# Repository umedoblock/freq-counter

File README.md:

# freq-counter
frequency counter with Attiny4313

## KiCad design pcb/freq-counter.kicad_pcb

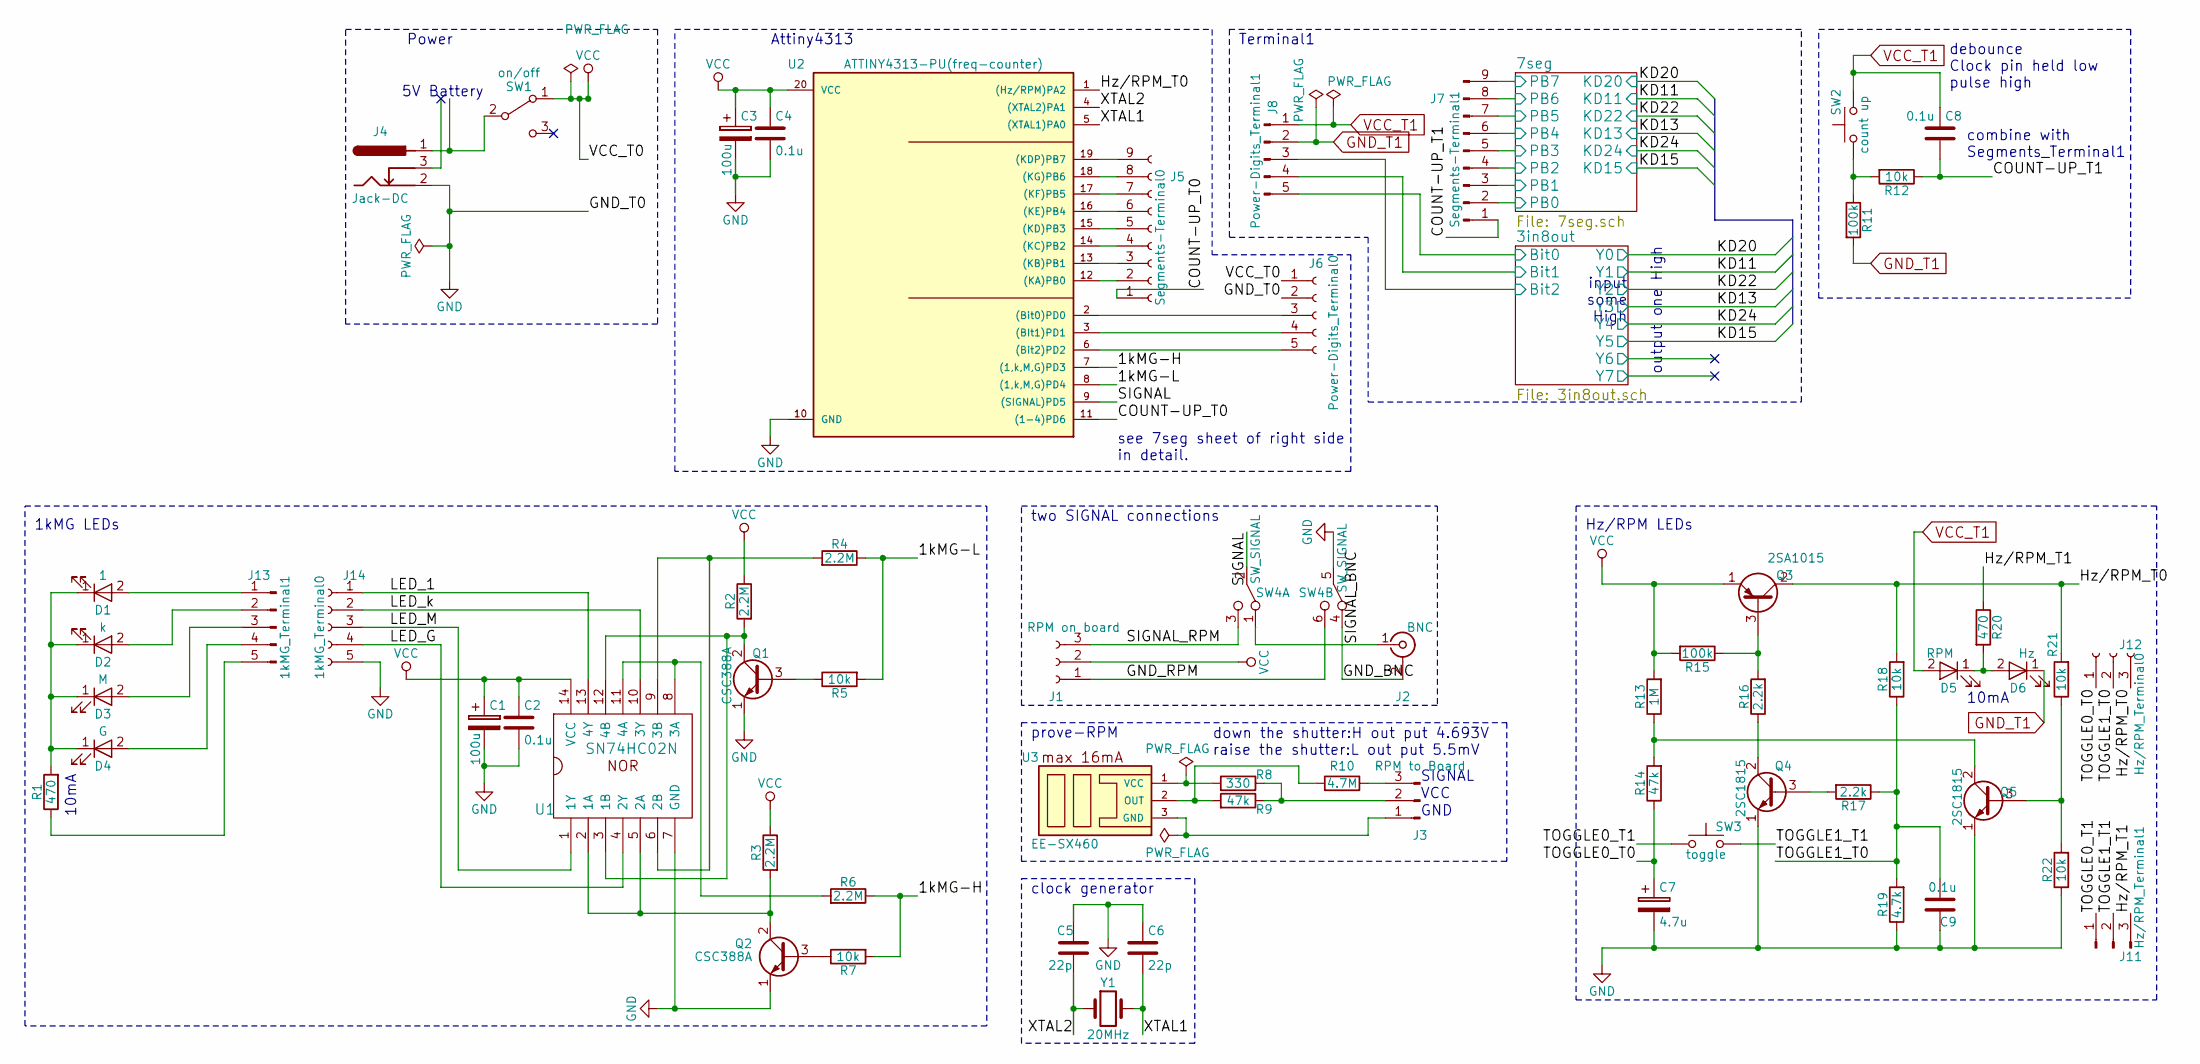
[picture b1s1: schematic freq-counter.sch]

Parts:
C1, C3: 100u; CP_Radial_D5.0mm_P2.50mm
C2, C4, C8, C9: 0.1u; C_Disc_D3.0mm_W1.6mm_P2.50mm
C5, C6: 22p; C_Disc_D3.0mm_W1.6mm_P2.50mm
C7: 4.7u; CP_Radial_D5.0mm_P2.50mm
D1: 1; LED_D5.0mm
D2: k; LED_D5.0mm
D3: M; LED_D5.0mm
D4: G; LED_D5.0mm
D5: RPM; LED_D5.0mm
D6: Hz; LED_D5.0mm
J1: RPM on board; PinHeader_1x03_P2.54mm_Horizontal
J2: BNC; BNC_Socket_TYCO-AMP
J3: RPM to Board; JST_XH_B03B-XH-A_03x2.50mm_Straight
J4: Jack-DC; BARREL_JACK
J5: Segments-Terminal0; PinSocket_1x09_P2.54mm_Vertical
J6: Power-Digits_Terminal0; PinSocket_1x05_P2.54mm_Vertical
J7: Segments-Terminal1; PinHeader_1x09_P2.54mm_Vertical
J8: Power-Digits_Terminal1; PinHeader_1x05_P2.54mm_Vertical
J11: Hz/RPM_Terminal1; PinHeader_1x03_P2.54mm_Vertical
J12: Hz/RPM_Terminal0; PinSocket_1x03_P2.54mm_Vertical
J13: 1kMG_Terminal1; PinHeader_1x05_P2.54mm_Vertical
J14: 1kMG_Terminal0; PinSocket_1x05_P2.54mm_Vertical
Q1, Q2: CSC388A; TO-92_Inline_Wide
Q3: 2SA1015; TO-92_Inline_Wide
Q4, Q5: 2SC1815; TO-92_Inline_Wide
R1, R20: 470; R_Axial_DIN0207_L6.3mm_D2.5mm_P7.62mm_Horizontal
R2, R3, R4, R6: 2.2M; R_Axial_DIN0207_L6.3mm_D2.5mm_P7.62mm_Horizontal
R5, R7, R12, R18, R21, R22: 10k; R_Axial_DIN0207_L6.3mm_D2.5mm_P7.62mm_Horizontal
R8: 330; R_Axial_DIN0207_L6.3mm_D2.5mm_P7.62mm_Horizontal
R9, R14: 47k; R_Axial_DIN0207_L6.3mm_D2.5mm_P7.62mm_Horizontal
R10: 4.7M; R_Axial_DIN0207_L6.3mm_D2.5mm_P7.62mm_Horizontal
R11, R15: 100k; R_Axial_DIN0207_L6.3mm_D2.5mm_P7.62mm_Horizontal
R13: 1M; R_Axial_DIN0207_L6.3mm_D2.5mm_P7.62mm_Horizontal
R16, R17: 2.2k; R_Axial_DIN0207_L6.3mm_D2.5mm_P7.62mm_Horizontal
R19: 4.7k; R_Axial_DIN0207_L6.3mm_D2.5mm_P7.62mm_Horizontal
SW1: on/off; SS12D01G4
SW2: count up; TVDT18-tactile-switch
SW3: toggle; TVDT18-tactile-switch
SW4: SW_SIGNAL; Slide-switch-x2
U1: SN74HC02N; DIP-14_W7.62mm
U2: ATTINY4313-PU(freq-counter); DIP-20_W7.62mm
U3: EE-SX460; EE-SX460-P1
Y1: 20MHz; Crystal_HC49-4H_Vertical

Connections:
/1kMG-H: R6.1, R7.2, U2.7 ((1,k,M,G)PD3)
/1kMG-L: R4.1, R5.2, U2.8 ((1,k,M,G)PD4)
/3in8out/Bit0: J8.5; also elsewhere on the board
/3in8out/Bit1: J8.4; also elsewhere on the board
/3in8out/Bit2: J8.3; also elsewhere on the board
/7seg/PB0: J7.2; also elsewhere on the board
/7seg/PB1: J7.3; also elsewhere on the board
/7seg/PB2: J7.4; also elsewhere on the board
/7seg/PB3: J7.5; also elsewhere on the board
/7seg/PB4: J7.6; also elsewhere on the board
/7seg/PB5: J7.7; also elsewhere on the board
/7seg/PB6: J7.8; also elsewhere on the board
/7seg/PB7: J7.9; also elsewhere on the board
/COUNT-UP_T0: J5.1, U2.11 ((1-4)PD6)
/COUNT-UP_T1: C8.2, J7.1, R12.1
/GND_BNC: J2.2 (Ext), SW4.4 (A)
/GND_RPM: J1.1, SW4.6 (C)
/Hz/RPM_T0: J12.3, Q3.2 (C), R18.2, R21.2, U2.1 ((Hz/RPM)PA2)
/Hz/RPM_T1: J11.3, R20.1
/LED_1: J14.1, U1.13 (4Y)
/LED_G: J14.4, U1.4 (2Y)
/LED_M: J14.3, U1.1 (1Y)
/LED_k: J14.2, U1.10 (3Y)
/SIGNAL: SW4.2 (B), U2.9 ((SIGNAL)PD5)
/SIGNAL_BNC: J2.1 (In), SW4.1 (A)
/SIGNAL_RPM: J1.3, SW4.3 (C)
/TOGGLE0_T0: C7.1, J12.1, R14.1
/TOGGLE0_T1: J11.1, SW3.1
/TOGGLE1_T0: C9.2, J12.2, R17.1, R18.1, R19.2
/TOGGLE1_T1: J11.2, SW3.2
/XTAL1: C6.2, U2.5 ((XTAL1)PA0), Y1.2
/XTAL2: C5.2, U2.4 ((XTAL2)PA1), Y1.1
GND: C1.2, C2.2, C3.2, C4.2, C5.1, C6.1, C7.2, C9.1, J4.2, J6.2, J14.5, Q1.1 (E), Q2.1 (E), Q4.1 (E), Q5.1 (E), R19.1, R22.1, SW4.5 (B), U1.7 (GND), U2.10 (GND)
GND_T1: D6.1 (K), J8.2, R11.2; also elsewhere on the board
unnamed: D1.1 (K), D2.1 (K), D3.1 (K), D4.1 (K), R1.2
unnamed: D1.2 (A), J13.1
unnamed: D2.2 (A), J13.2
unnamed: D3.2 (A), J13.3
unnamed: D4.2 (A), J13.4
unnamed: D5.1 (K), D6.2 (A), R20.2
unnamed: J3.1, U3.3 (GND)
unnamed: J3.2, R8.1, R9.1
unnamed: J3.3, R10.1
unnamed: J4.1, SW1.2 (B)
unnamed: J5.2, U2.12 ((KA)PB0)
unnamed: J5.3, U2.13 ((KB)PB1)
unnamed: J5.4, U2.14 ((KC)PB2)
unnamed: J5.5, U2.15 ((KD)PB3)
unnamed: J5.6, U2.16 ((KE)PB4)
unnamed: J5.7, U2.17 ((KF)PB5)
unnamed: J5.8, U2.18 ((KG)PB6)
unnamed: J5.9, U2.19 ((KDP)PB7)
unnamed: J6.3, U2.2 ((Bit0)PD0)
unnamed: J6.4, U2.3 ((BIt1)PD1)
unnamed: J6.5, U2.6 ((Bit2)PD2)
unnamed: J13.5, R1.1
unnamed: Q1.2 (C), R2.2, U1.3 (1B), U1.12 (4B)
unnamed: Q1.3 (B), R5.1
unnamed: Q2.2 (C), R3.2, U1.2 (1A), U1.5 (2A)
unnamed: Q2.3 (B), R7.1
unnamed: Q3.3 (B), R15.1, R16.2
unnamed: Q4.2 (C), R16.1
unnamed: Q4.3 (B), R17.2
unnamed: Q5.2 (C), R13.1, R14.2
unnamed: Q5.3 (B), R21.1, R22.2
unnamed: R4.2, U1.6 (2B), U1.9 (3B)
unnamed: R6.2, U1.8 (3A), U1.11 (4A)
unnamed: R8.2, U3.1 (VCC)
unnamed: R9.2, R10.2, U3.2 (OUT)
unnamed: R11.1, R12.2, SW2.1
VCC: C1.1, C2.1, C3.1, C4.1, J1.2, J6.1, Q3.1 (E), R2.1, R3.1, R13.2, R15.2, SW1.1 (A), U1.14 (VCC), U2.20 (VCC)
VCC_T1: C8.1, D5.2 (A), J8.1, SW2.2; also elsewhere on the board

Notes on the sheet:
debounce Clock pin held low pulse high
Hz/RPM LEDs
1kMG LEDs
10mA
output one High
input some High
see 7seg sheet of right side in detail.
Attiny4313
clock generator
prove-RPM
two SIGNAL connections
SIGNAL
VCC
GND
down the shutter:H out put 4.693V raise the shutter:L out put 5.5mV
Power
5V Battery
Terminal1
combine with Segments_Terminal1

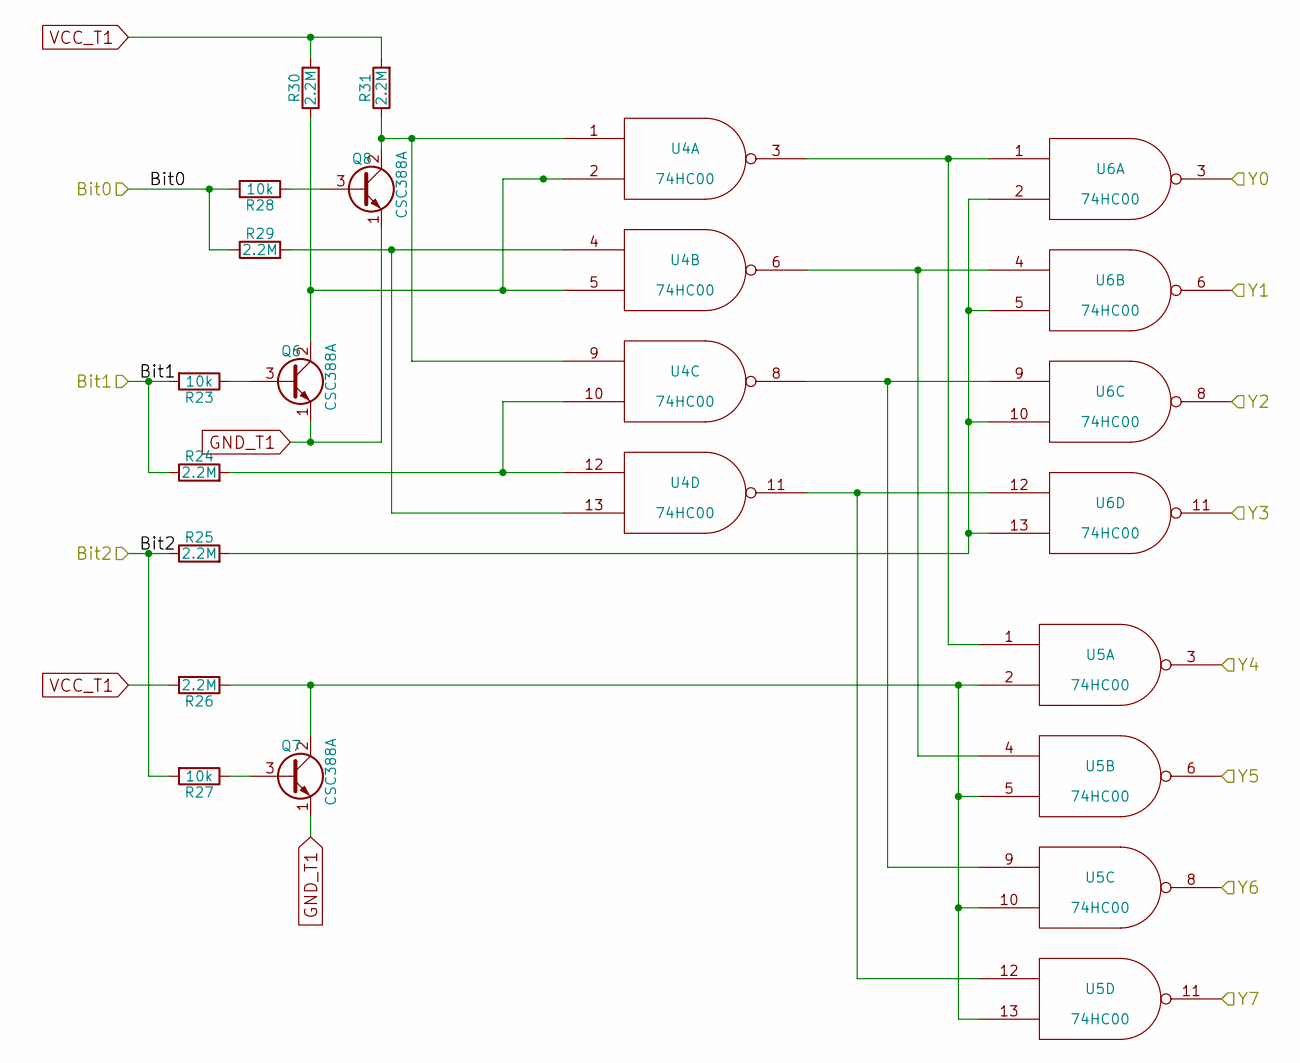
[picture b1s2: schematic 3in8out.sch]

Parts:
Q6, Q7, Q8: CSC388A; TO-92_Inline_Wide
R23, R27, R28: 10k; R_Axial_DIN0207_L6.3mm_D2.5mm_P7.62mm_Horizontal
R24, R25, R26, R29, R30, R31: 2.2M; R_Axial_DIN0207_L6.3mm_D2.5mm_P7.62mm_Horizontal
U4, U5, U6: 74HC00; DIP-14_W7.62mm

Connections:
/3in8out/Bit0: R28.2, R29.1; also elsewhere on the board
/3in8out/Bit1: R23.2, R24.1; also elsewhere on the board
/3in8out/Bit2: R25.1, R27.2; also elsewhere on the board
/KD11: U6.6; also elsewhere on the board
/KD13: U6.11; also elsewhere on the board
/KD15: U5.6; also elsewhere on the board
/KD20: U6.3; also elsewhere on the board
/KD22: U6.8; also elsewhere on the board
/KD24: U5.3; also elsewhere on the board
GND_T1: Q6.1 (E), Q7.1 (E), Q8.1 (E), U4.7 (GND_T1), U5.7 (GND_T1), U6.7 (GND_T1); also elsewhere on the board
unnamed: Q6.2 (C), R30.1, U4.2, U4.5
unnamed: Q6.3 (B), R23.1
unnamed: Q7.2 (C), R26.1, U5.2, U5.5, U5.10, U5.13
unnamed: Q7.3 (B), R27.1
unnamed: Q8.2 (C), R31.1, U4.1, U4.9
unnamed: Q8.3 (B), R28.1
unnamed: R24.2, U4.10, U4.12
unnamed: R25.2, U6.2, U6.5, U6.10, U6.13
unnamed: R29.2, U4.4, U4.13
unnamed: U4.3, U5.1, U6.1
unnamed: U4.6, U5.4, U6.4
unnamed: U4.8, U5.9, U6.9
unnamed: U4.11, U5.12, U6.12
VCC_T1: R26.2, R30.2, R31.2, U4.14 (VCC_T1), U5.14 (VCC_T1), U6.14 (VCC_T1); also elsewhere on the board

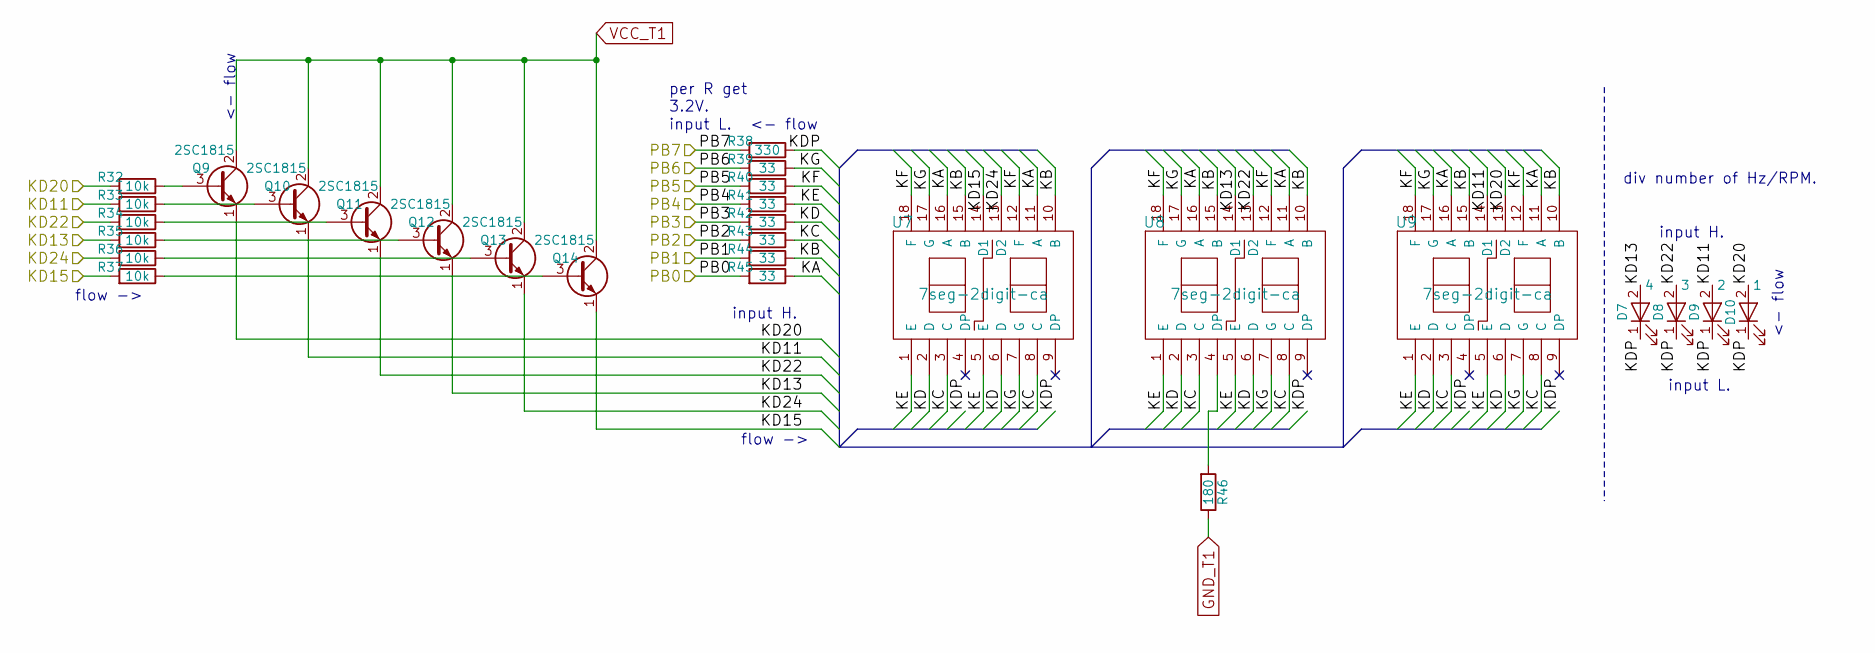
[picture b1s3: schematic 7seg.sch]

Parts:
D7: 4; LED_D5.0mm
D8: 3; LED_D5.0mm
D9: 2; LED_D5.0mm
D10: 1; LED_D5.0mm
Q9, Q10, Q11, Q12, Q13, Q14: 2SC1815; TO-92_Inline_Wide
R32, R33, R34, R35, R36, R37: 10k; R_Axial_DIN0207_L6.3mm_D2.5mm_P7.62mm_Horizontal
R38: 330; R_Axial_DIN0207_L6.3mm_D2.5mm_P7.62mm_Horizontal
R39, R40, R41, R42, R43, R44, R45: 33; R_Axial_DIN0207_L6.3mm_D2.5mm_P7.62mm_Horizontal
R46: 180; R_Axial_DIN0207_L6.3mm_D2.5mm_P7.62mm_Horizontal
U7, U8, U9: 7seg-2digit-ca; PARA_LIGHT-552SRD

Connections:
/7seg/KA: R45.1, U7.11 (A), U7.16 (A), U8.11 (A), U8.16 (A), U9.11 (A), U9.16 (A)
/7seg/KB: R44.1, U7.10 (B), U7.15 (B), U8.10 (B), U8.15 (B), U9.10 (B), U9.15 (B)
/7seg/KC: R43.1, U7.3 (C), U7.8 (C), U8.3 (C), U8.8 (C), U9.3 (C), U9.8 (C)
/7seg/KD: R42.1, U7.2 (D), U7.6 (D), U8.2 (D), U8.6 (D), U9.2 (D), U9.6 (D)
/7seg/KDP: D7.1 (K), D8.1 (K), D9.1 (K), D10.1 (K), R38.1
/7seg/KE: R41.1, U7.1 (E), U7.5 (E), U8.1 (E), U8.5 (E), U9.1 (E), U9.5 (E)
/7seg/KF: R40.1, U7.12 (F), U7.18 (F), U8.12 (F), U8.18 (F), U9.12 (F), U9.18 (F)
/7seg/KG: R39.1, U7.7 (G), U7.17 (G), U8.7 (G), U8.17 (G), U9.7 (G), U9.17 (G)
/7seg/PB0: R45.2; also elsewhere on the board
/7seg/PB1: R44.2; also elsewhere on the board
/7seg/PB2: R43.2; also elsewhere on the board
/7seg/PB3: R42.2; also elsewhere on the board
/7seg/PB4: R41.2; also elsewhere on the board
/7seg/PB5: R40.2; also elsewhere on the board
/7seg/PB6: R39.2; also elsewhere on the board
/7seg/PB7: R38.2; also elsewhere on the board
/KD11: D9.2 (A), Q10.1 (E), R33.2, U9.14 (D1); also elsewhere on the board
/KD13: D7.2 (A), Q12.1 (E), R35.2, U8.14 (D1); also elsewhere on the board
/KD15: Q14.1 (E), R37.2, U7.14 (D1); also elsewhere on the board
/KD20: D10.2 (A), Q9.1 (E), R32.2, U9.13 (D2); also elsewhere on the board
/KD22: D8.2 (A), Q11.1 (E), R34.2, U8.13 (D2); also elsewhere on the board
/KD24: Q13.1 (E), R36.2, U7.13 (D2); also elsewhere on the board
GND_T1: R46.1; also elsewhere on the board
unnamed: Q9.3 (B), R32.1
unnamed: Q10.3 (B), R33.1
unnamed: Q11.3 (B), R34.1
unnamed: Q12.3 (B), R35.1
unnamed: Q13.3 (B), R36.1
unnamed: Q14.3 (B), R37.1
unnamed: R46.2, U8.4 (DP)
VCC_T1: Q9.2 (C), Q10.2 (C), Q11.2 (C), Q12.2 (C), Q13.2 (C), Q14.2 (C); also elsewhere on the board

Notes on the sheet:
per R get 3.2V.
div number of Hz/RPM.
input L.
input H.
flow ->
<- flow

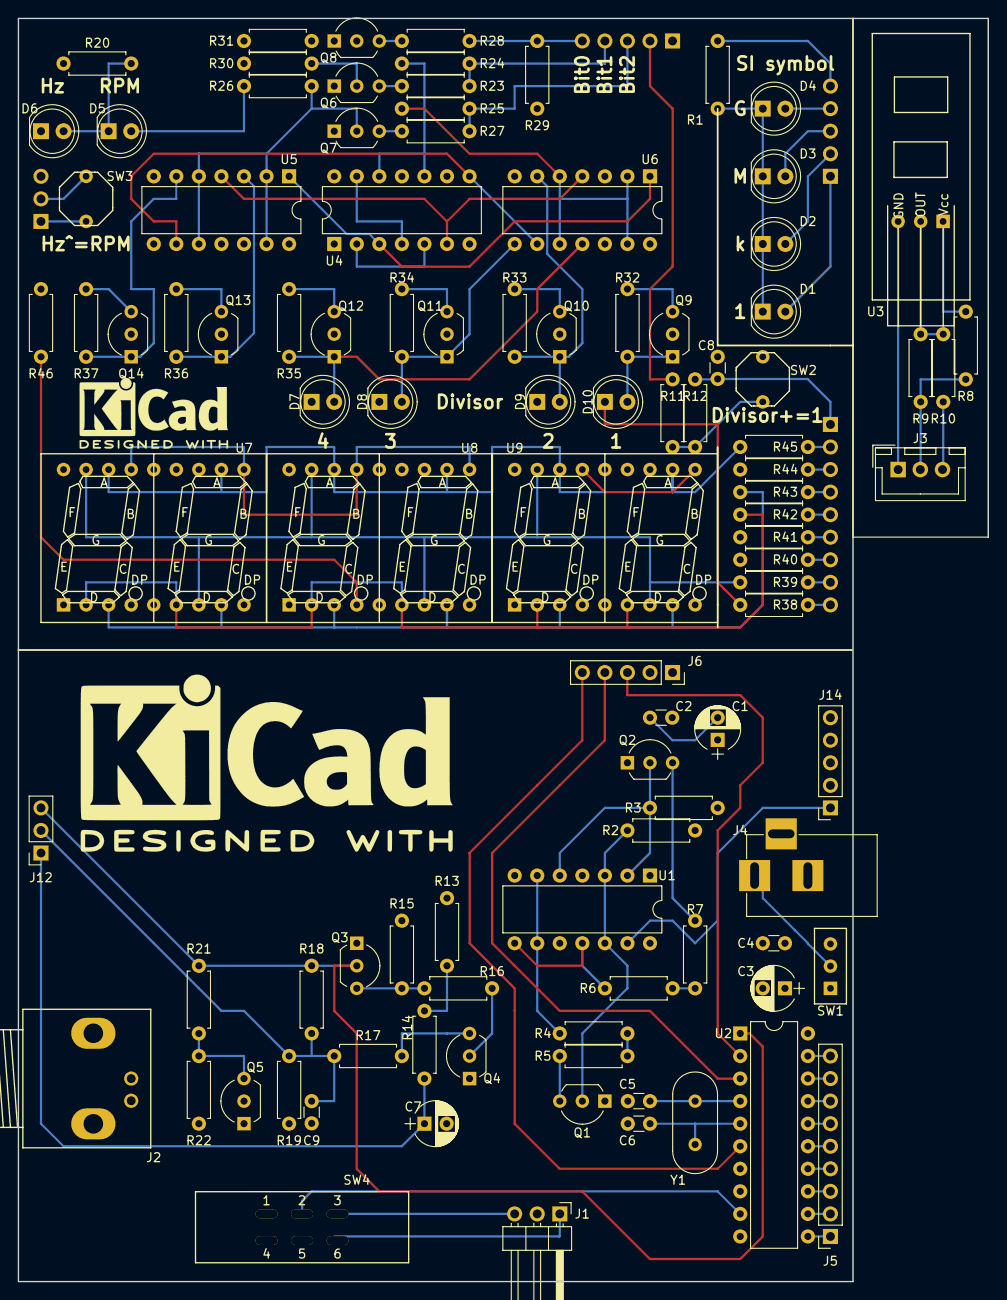
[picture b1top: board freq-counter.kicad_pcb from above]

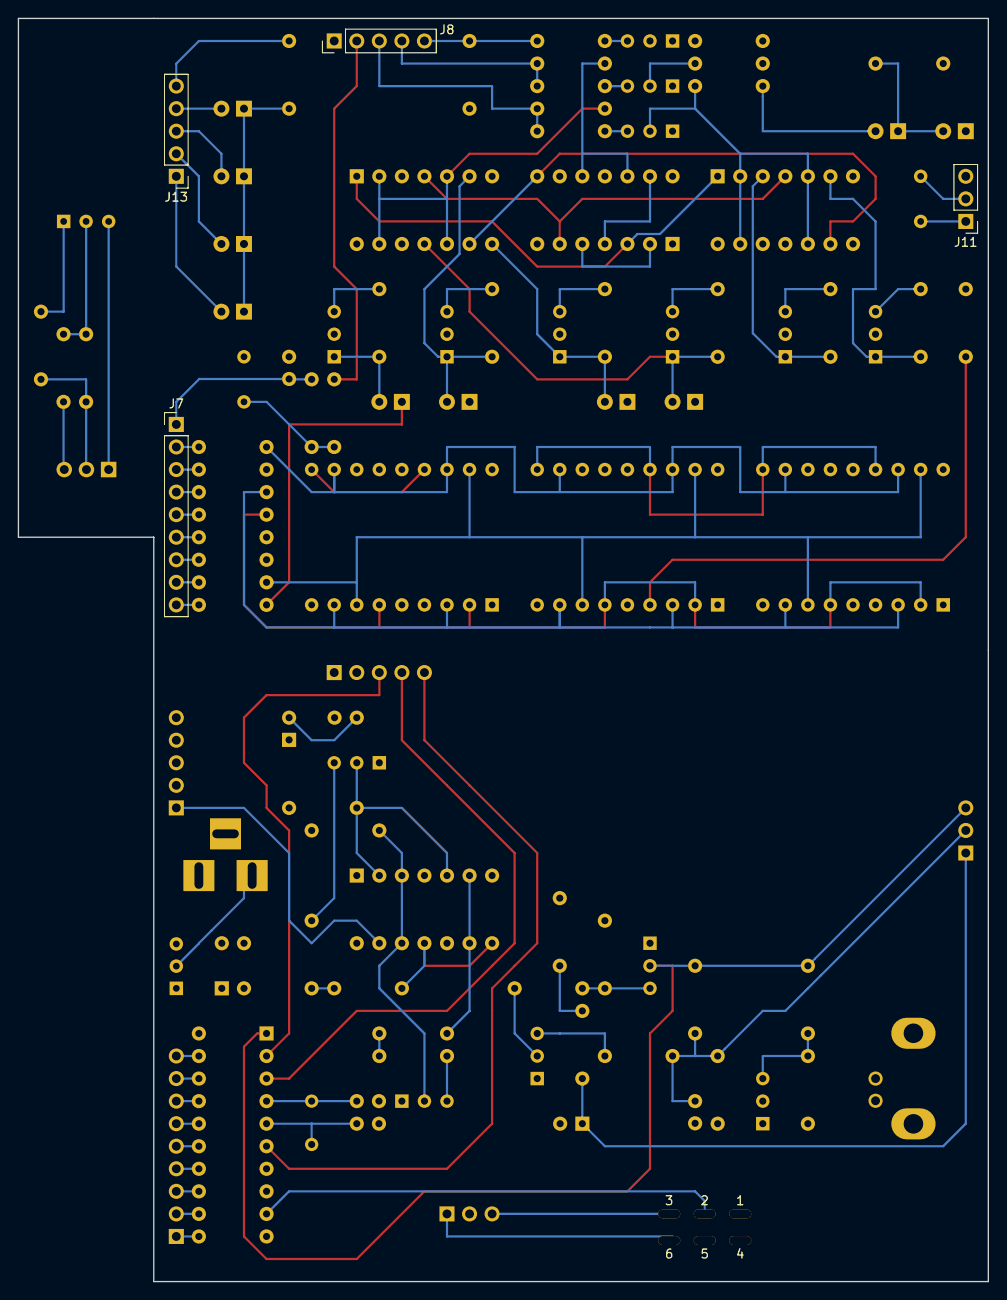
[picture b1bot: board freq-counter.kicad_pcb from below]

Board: 4 copper layers, 109.2 x 142.2 mm, 105 parts (4 on the bottom side), 106 nets.

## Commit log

2017-11-17 Attiny4313 の pin assign.
2017-11-17 ignore last of # file.
2017-11-17 add files.
2017-11-17 3入力8出力を大雑把に書いた。
2017-11-18 tempolary save.
2017-11-18 3入力8出力回路を書いた。8出力の内，6出力は7segの各桁に対応するよう繋いだ。
    残りの2出力は未結線とした。
2017-11-18 rename Digits6.sch to 3in8out.sch.
2017-11-18 7seg に関する部分をsheetに分割。
2017-11-18 change arrangement.
2017-11-18 7seg の DIG-1,2 を 2SC1815 経由で VCC と繋ぐようにした。
    最初は TVCC と DIG-1,2 の接続にしていたが，7segで100mA消費すると仮定すると，
    回路全体で150mA中の130mA使用する計算になり，残りの電流が20mA程度になってしまう。
    なぜならば，thyristor を構成する2SA1015, 2SC1815で供給出来る電流を150mAと
    計算しているから。
2017-11-18 write clock generator.
2017-11-18 透過型フォト・マイクロセンサ EE-SX460 を追加。
2017-11-18 add explain "max 16mA".
2017-11-18 EE-SX460 shrinked.
2017-11-18 write just SIGNAL of photo interrupt block.
2017-11-19 SIGNAL を BNC端子 に接続することにした。
2017-11-19 determined two type connections to SIGNAL.
2017-11-19 prove-RPM 回路の定数を決定。
2017-11-19 1kMG LEDs の LED に使用する抵抗を一つのみにした。
    1kMGのLEDの内，一つのみ光るから，4個も必要ない。
2017-11-19 clock-generator の図に隙間が空いていて美しくなかったので，引き締めた。
2017-11-19 block diagram の配置を微調整。
2017-11-19 add Power part and pass con to Attiny4313 of VCC.
2017-11-19 7seg sheet に TVCC を global label として設定。
2017-11-19 add global label of "TVCC" in Power part.
2017-11-19 annotate.
2017-11-19 wire に未接続の設定をしていたら文句を言われたので，wireの未接続を削除。
2017-11-19 細々した配線誤りを修正。 fixed tiny mistake.
2017-11-20 add footprint of PARA_LIGHT_CA 551/552 SRD.
2017-11-20 EE-SX460-P1 の footprint を書いた。
2017-11-21 mini mini universal board.
2017-11-22 make 7segments 551SR-C/A model.
2017-11-22 add legs to 551SR-C/A.
2017-11-22 Para light 552SR の model も書いた。
2017-11-22 rename 551SR-CA to 551SR.
2017-11-22 move to axis of z +0.1 unit.
2017-11-22 rename for delete "_CA".
2017-11-22 segment の色がおかしかったので修正。
2017-11-22 とりあえず，押しボタン部分と胴体が基板に正しい大きさで接地する。
2017-11-22 add Tactile model and footprint.
2017-11-22 ee-sx640 の 3D model の get 方法を書いた。
2017-11-22 全ての部品を展開しただけの状態。
2017-11-22 ignore omron file.
2017-11-22 slide switch 3D model.
2017-11-22 OMRON 提供の EE-SX460 の 3D に合わせて，縮尺・回転・off set を適切に調整した。
2017-11-22 抵抗を 6.3mm の 1 / 4 W の抵抗に変更。
2017-11-22 3in8out 回路に CvPcb で部品を割り当てた。
2017-11-22 CvPcb で main 基板に部品を割り当てた。
2017-11-22 KiCad が自動的に修正。
2017-11-22 PcbNew で全ての部品を展開した状態。他は何もしていない。
2017-11-23 P1 <=> P11 の入れ替え。P1をHz/RPMの入力用PIN。P11を1-4のcount up PIN にした。
    他に，P1, 19,-12, 2,3,6,7,8を入力PINに設定。何故か，入出力になっていた。
2017-11-24 2SC1815 の footprint を，足の間隔が0.1inchのfootprintに変更。
2017-11-24 uni板は，24x31 のuni板を作成。2桁7SEGは，中央の縦線を削除。
    2桁7SEGでは，上下を水平に走る線を2本から1本に変更。
2017-11-24 2SC1815 のfootprintを，足の感覚が0.1inchであるfootprintに変更。
2017-11-24 P1 <=> P11 の入れ替え。P7<=>P8の入れ替え。
    詳細は以下の通り。
    1 PA2 Hz/RPM入力
    11 PD6 1/2/3/4切り替え
    7 PD3 '1/k/M/G表示 H
    8 PD4 '1/k/M/G表示 L
2017-11-24 P2,3,6-8,12-19を入力PINに設定。P7<->P8を入れ替え。P1<->P11を入れ替え。
    P1をHz/RPMの入力用に。P11をDivisor(1-4)用に設定。
    P7を1,k,M,GのHに。P8を1,k,M,GのLに設定。
2017-11-24 変更点多し。
    修正は色々よ。色々。
2017-11-24 基板の配線を9割ぐらい終えた。現状では，基板の実装面積が大きくなり困っている。
    機能毎に複数階にしようか検討中。各回はcableで繋ぐことを想定している。
2017-11-24 D5 と接続する"TVCC"の向きを垂直から水平に修正。
2017-11-25 RPM, BNCのGND線とSIGNAL線をSW_DPDTで物理的に切り離すようにした。
2017-11-25 tow SIGNAL connections の配置を修正。その他，見栄えを良くするための整形をした。
2017-11-25 回路図の見栄えを良くするために，リファレンスを回転させたり移動させたり。
2017-11-25 SW4A,SW4Bの定数が異なっていたので，"SW_SIGNAL"に統一。
2017-11-25 "SW4" "SW_SIGNAL" に，"freq-counter:Slide-switch" を割り当てた。
2017-11-25 slide switch の footprint を 3x2に修正。 3x1は間違いだった。
2017-11-25 delete.
2017-11-25 slide switch を2回路2接点に修正。
    私の手持ちのslide switchは2回路2接点だったため。
2017-11-25 slide switchを2回路2接点に修正。
2017-11-26 ignore stl file.
2017-11-28 make Toggle switch of footprint and 3D model.
2017-11-28 auto changed by kicad.
2017-11-28 add three legs to toggle switch.
2017-11-28 "freq-counter:SW_Toggle_x1" を SW1(on/off) として採用。
2017-11-28 SW1(on/off), SW4(GND,SIGNAL)を基板上に仮配置した。
2017-11-28 SW4Aの1-3, SW4Bの4-6の配線をそれぞれ繋ぎ変え。それらの配線にlabelを設定。
    基板実装上，入れ替えたほうがslideの操作が直感的であったため。
    PcbnewでSW4A,SW4Bの配線が何の意味の配線か分かりにくかったため以下のlabelを設定。
    1: SIGNAL_BNC
    3: SIGNAL_RPM
    4: GND_BNC
    6: GND_RPM
2017-11-28 SW4(SW_SIGNAL) の1-3, 4-6の配線を入れ替え。
2017-11-28 U2(Attiny4313)の8PINのlabel名を1kMG-Lに修正。いつの間にか変わっていた。
2017-11-28 U2(Attiny4313)の8PINのlabel名を1kMG-Lに修正。
    いつの間にか変わっていた。。。
2017-11-29 J3(EE-SX460) を別基板に切り分けて実装した。RPMの計測用sensor。
2017-11-29 RPM 用基板を母基板にくっつけた。
2017-11-29 Bit0, Bit1, Bit2 のlabelを振った。
2017-11-29 基本的に入出力に関する，7SEG, LED, PUSH-BUTTONを2階に配置する。
    2階-1階の直登戦術でいこうと思う。
2017-11-29 4 layer に設定。In1.Cuがjumper layer，In2.Cuが電源layer。
2017-11-29 7SEG, LED, PUSH-BUTTON 等の入出力関係は上部に移動させた。
2017-11-29 74HC00系用に，VCC_T1, GND_T1を作成。
    母板と74HC00をconnectorで分離したかったため，xxx_T1を作成する必要があった。
2017-11-29 ERC 走らせたら，いくつか error を指摘されたので修正。
2017-11-29 TVCC, TGND の壊滅。
2017-11-29 4色駆使することで，なんとかかんとか7SEG, LEDの配線が完成。
2017-11-29 Display 部を時計回りに90度回転させて，mother部とくっつけた。
    なんとか，2階建てで上手くいきそうな気がする。
2017-11-29 母板部の配線を進めた。Display部を決定したいので，中途半端だがcommit。
2017-11-29 Display部の配線は完成。
2017-11-29 Display 部を決定。これに合わせて母板を設計する。
2017-11-29 Display板の大きさ，向きが決まった。Displayに合わせて母板を仕上げる。
2017-11-29 Display部に，Hz/RPM用のLEDとPUSH-BUTTONを移動させた。Display部は，本当に完成。
2017-11-29 Display 部にLED用の電流制限抵抗を移動させた。Display部のtestをしやすくするため。
2017-11-29 1kMGの電流制限抵抗(R1)の配置を水平から垂直に変更。
2017-11-29 Display部の Hz/RPM をTerminal接続にした。
2017-11-30 Hz/RPM のterminal化が完成。
    他にもpackages3dの設定や，footprintの設定を変えたりするなど。
    余計な手間を掛けていると思える。
2017-11-30 1kMG-LED 部のTerminal化が完了。
2017-11-30 LED に関してのCvPcbをやり直した。
2017-11-30 transistor には，CvPcbをやり直した。
2017-11-30 count-up を Terminal 化した。
2017-11-30 combine Segments-Terminal? and count-up-Terminal?
2017-11-30 余分な配線やビヤを削除。その他，不必要となった箇所を削除。
2017-11-30 上階のDisplay部は配線が完了したと考えている。
    あとは，上階のPinHeaderに合わせて，下階のPinSocketを配置して配線を頑張るだけ。
2017-11-30 Terminal0 系を配置。
    後は上手く配線をするだけ。
2017-11-30 Terminal0系をlock。 Hz/RPMの部品をHz/RPM-Terminal0付近に配置。
2017-11-30 基板外形を決定。Terminal0の位置も決定し，Lockしておいた。
    なんとか上手く２階建てにできそう。
2017-11-30 １階の母板に実装する部品の位置を決定。
    あとは，１階の配線が決定すれば実装に移れる。
2017-11-30 １階の配線の大部分が終了。残るは，ICとTerminal0の配線。
    1kMG LED については，1 <-> k, M <-> G の入れ替えをそれぞれした方が良いと分かった
    ので，次の commit で修正しておく。
2017-11-30 SN74HC02N(U1)の，LED_1 <-> LED_k, LED_M <-> LED-G の配線をそれぞれ入れ替えた。
2017-11-30 １階・２階・Terminal0 <-> Terminal1 の全てにおいて配線完了。
2017-11-30 なんでこんなdiffが？
2017-11-30 Power-Digtis_Terminal1 を作成。Power, Digits の Terminal1 を連結させた。
    Connectors_JSTを使っても取り外しを出来るのは，
    １階と２階の基板を離してからだと思ったので近くにいた，Digits系と繋げてしまった。
    こっちの方が強度を出せると思うため。
2017-11-30 ほぼ完成。電源ON/OFFの switch を slide switch に変更する必要があるけど保留。
2017-11-30 実装には進んで良い板。但し，Silkの向き・位置の修正など細々した修正が必要。
2017-11-30 基板画像が汚かったので撮り直した。
2017-12-01 slide switch 1P2T.
2017-12-01 SK-12D01-VG4 (小型 slide switch) の footprint, 3D model 作った。
2017-12-01 SS12D01G4(slide switch) の足が基板から出るように修正。footprint も作成。
2017-12-01 自作の3D modelを使う時，pathを${KIPROJMOD}からの相対pathで指定するようにした。
2017-12-01 3D model のpathを指定する方法を，KIPROJMOD環境変数からの相対pathに変更。
    今までは絶対pathで指定していた。
2017-12-01 KIPRJMOD が正しく， KIPROJMOD は誤り。
2017-12-01 Power ON/OFF switch を slide switch に変更。
2017-12-01 RPM on board を PinHeaderに変更。
    手持ちの部品にJST_XH_B03B-XH-A_1x03_P2.50mmの横向きがなかったため。
2017-12-01 ON/OFF の slide switch を横型に変更。
2017-12-01 slide switch(横型) の footprint で，3PINが四角だったので，丸に修正。
2017-12-01 silk の配置・回転を完了させた。
2017-12-01 toggle に関する部品を手前側に移動させて，奥側に空間を用意するようにした。
    後々，電池を配置できればいいなと思っている。
2017-12-01 取り急ぎ，基板外形の縦の大きさを１階・２階ともに2.8inchとした。0.1inch縮めた。
2017-12-01 基板外形だけは修正している。
2017-12-01 基板外形を縦0.1inch縮めた配線を完了。
    しかし，横も0.1inchでかいと気付いてしまった。
    こっちは難しそうだ。
2017-12-01 取り急ぎ，基板外形の横を3.7inchとした。横も0.1inch縮めた。
2017-12-02 Power ON/OFF の slide switch を横型から縦型に変更。
2017-12-02 BarrelJack-DC の footprint が削除されていたので復活させた。
2017-12-02 旧式の footprint, packages3D を大復活させた。
2017-12-02 民族大移動。
2017-12-02 細々とした配線の最適化を施した。
2017-12-02 左辺の基板外形の２階と１階の端点が一致するよう修正。
    基板外形を上手く決定できなくて error を出力していたので
2017-12-02 3Dpackages が表示されるように，旧式の3D modelを使うようにした。
2017-12-02 ２階のsilkの整理が終わった。
2017-12-02 １階のsilkの修正も完了。
2017-12-02 footprint の定数の位置や向きを修正。綺麗になった。良かった。
    実装する時に分かりやすいと思う。
2017-12-02 細々とした配線の修正。
2017-12-02 clock(Y1) を 20MHz とした。
2017-12-02 部品表。
2017-12-02 基板の１階と２階にKiCadのLogoを入れて本当に完成。
2017-12-02 忘れ物。
2017-12-07 BNC connector(B-057-HP)の大きさに合わせた形を作った。
    case に穴を開ける時に使う。
    参考:
    http://akizukidenshi.com/catalog/g/gC-00134/
2017-12-08 3mm hole.
2017-12-08 完成した基板と，image board by KiCad .
2017-12-08 moved.
2017-12-08 almost done. caseが粗方完成。
2017-12-09 細々した部品を書いている。stoodとか。押しbuttonとか。
    残りは，前面の Signal/RPM 切り替え用の bar くらい。
2017-12-09 cube like a lego.
2017-12-09 make a cube with hight of 10mm board.
2017-12-09 1面と3面の両脇のホゾが完成。
2017-12-09 5, 6面のホゾを作成。
2017-12-09 BNC connector design.
2017-12-09 freq-counter のcaseが完成。
2017-12-09 EE-SX640 を使ってRPM計測する時のために，右側にcaseを作った。
2017-12-09 空いている部分にcube用のpieceを作った。
2017-12-10 Hz/RPM切り替え用のswitch()を切り出すようにした。空き場所にblockを作った。
    この板で切ってしまう。
2018-07-24 KiCad 5.0 change some files.
